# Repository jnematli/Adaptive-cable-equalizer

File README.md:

# GS3440-Adaptive-cable-equalizer
This project was a part of my Hardware Design course at KU Leuven Campus Group T. The PCB was built using Autodesk Eagle.

PCB top side:

PCB bottom side:

50 Ohm transmission line:

75 Ohm transmission line:

Design rules:

•	The outputs should be symmetrical, the transmission lines at the output should be of the same size.

•	Put components closer to the IC to minimize loop area.

•	Put decoupling capacitors for Vcc to reduce noise.

•	Put transistor to the side of the PCB for the possibility to attach a heat sink.

•	Thermal spacing (already mentioned in the DRC).

## License

All design files in this repository are released under the [GNU General Public License version 3 (GPL-3.0)](LICENSE). They can be freely used for personal projects where this device can be of use.

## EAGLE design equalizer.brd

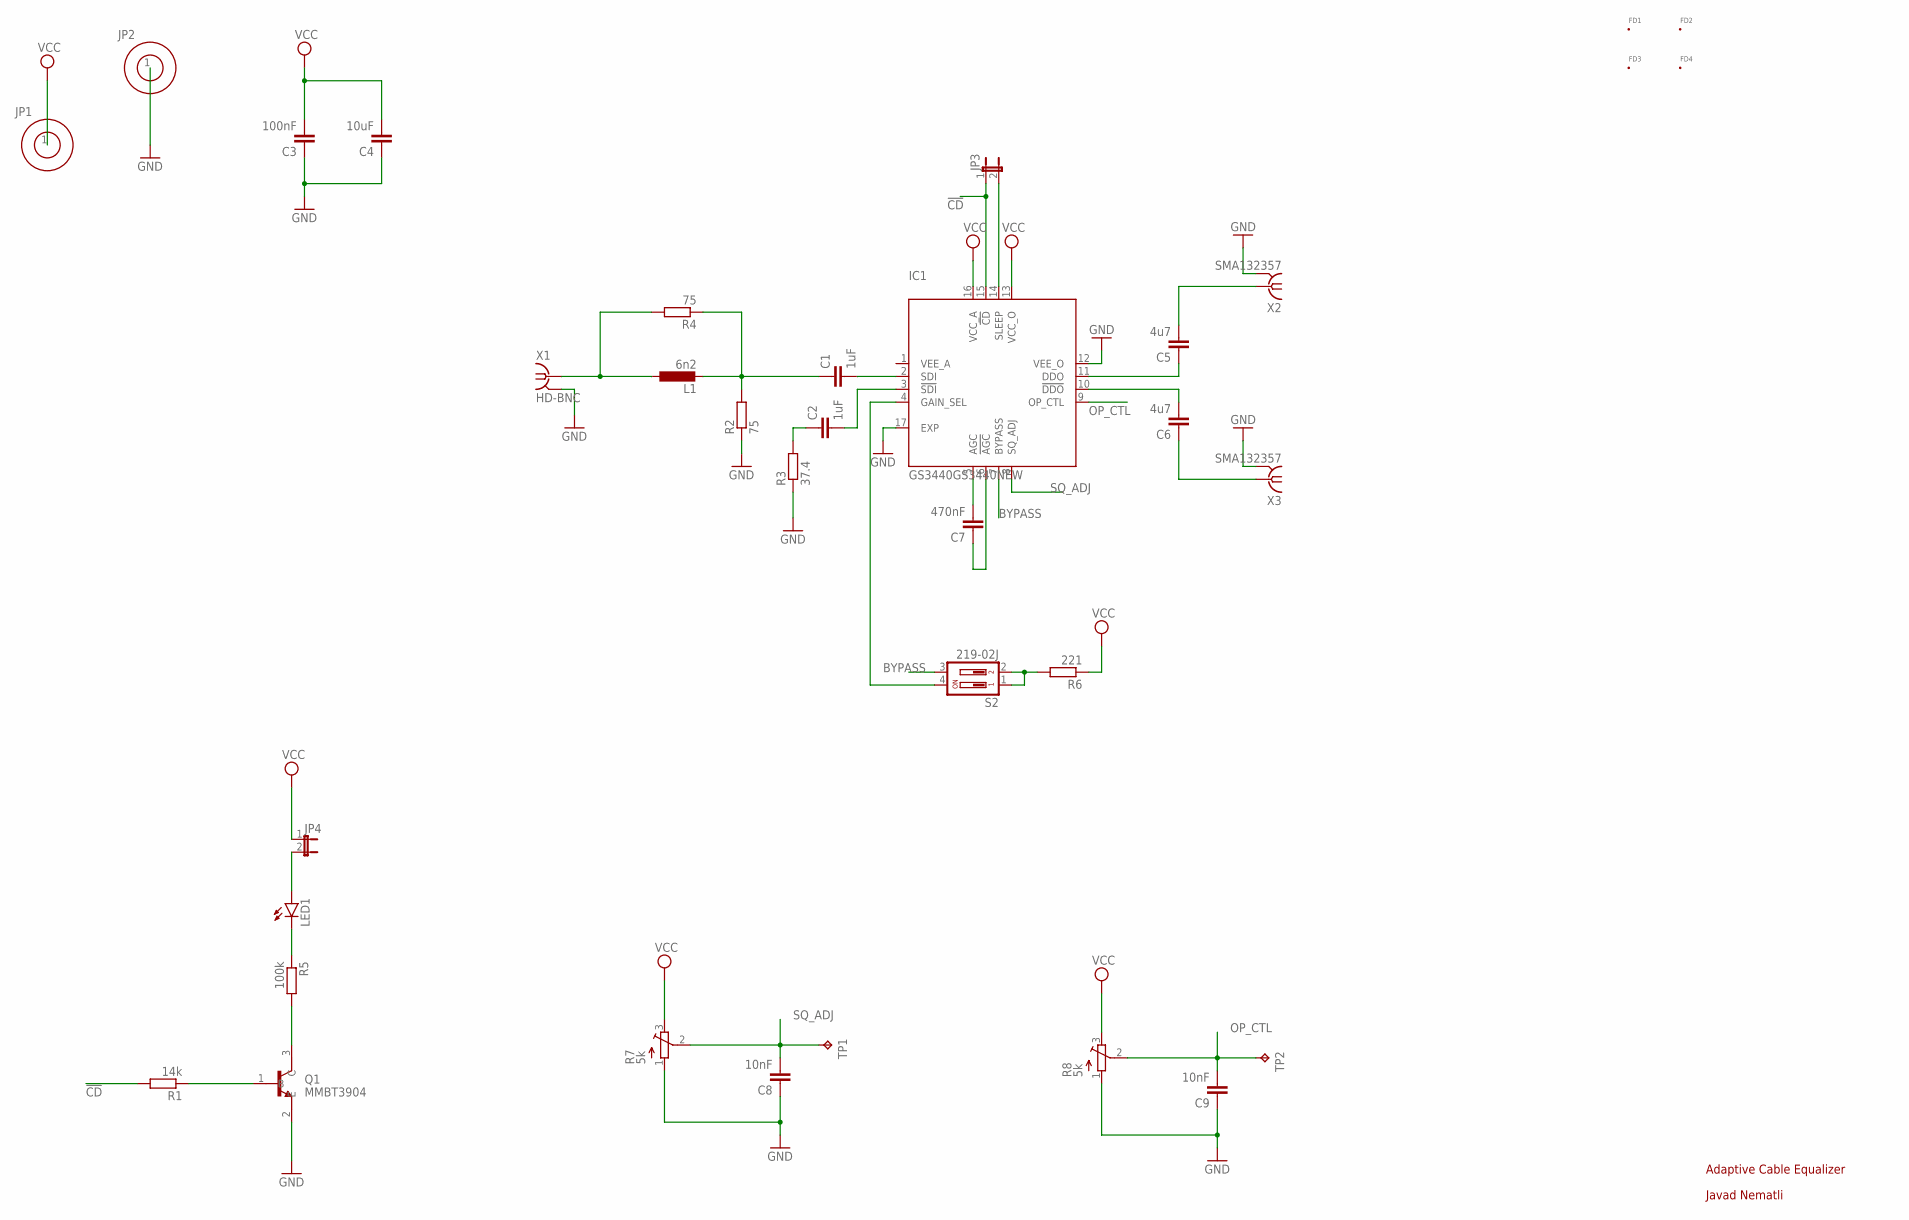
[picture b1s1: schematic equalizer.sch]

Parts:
C1, C2: 1uF; 0402
C3: 100nF; 0402
C4: 10uF; 0402
C5, C6: 4u7; 0402
C7: 470nF; 0402
C8, C9: 10nF; 0402
FD1, FD2, FD3, FD4: FID_20MIL; FID_020
IC1: GS3440GS3440NEW; QFN65P400X400X90-17T260N
JP1, JP2: 4MMSOCKET; 4MM
JP3, JP4: JP1E; JP1
L1: 6n2; 0402
LED1: LEDCHIP-LED0805; CHIP-LED0805
Q1: MMBT3904; SOT95P240X120-3N
R1: 14k; 0402
R2, R4: 75; 0402
R3: 37.4; 0402
R5: 100k; 0402
R6: 221; 0402
R7, R8: 5k; 3223W
S2: 219-02J; CTS-219-02J
TP1, TP2: TPTP06R; TP06R
X1: HD-BNC; 034_1018_12G
X2, X3: SMA132357; SMA

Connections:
!CD: IC1.15 (!CD), JP3.1, R1.2
BYPASS: IC1.7 (BYPASS), S2.3
GND: C3.1, C4.1, C8.1, C9.1, IC1.12 (VEE_O), IC1.17 (EXP), JP2.1, Q1.2 (E), R2.1, R3.1, R7.1 (A), R8.1 (A), X1.G@1 (2), X1.G@2 (2), X1.G@3 (2), X1.G@4 (2), X2.G@1 (2), X2.G@2 (2), X2.G@3 (2), X2.G@4 (2), X3.G@1 (2), X3.G@2 (2), X3.G@3 (2), X3.G@4 (2)
unnamed: C1.2, IC1.2 (SDI)
unnamed: C1.1, L1.2, R2.2, R4.1
unnamed: C2.1, R3.2
unnamed: C2.2, IC1.3 (!SDI)
unnamed: L1.1, R4.2, X1.P$1 (1)
unnamed: C5.1, IC1.11 (DDO)
unnamed: C5.2, X2.1
unnamed: C6.2, IC1.10 (!DDO)
unnamed: C6.1, X3.1
unnamed: C7.2, IC1.5 (AGC)
unnamed: C7.1, IC1.6 (!AGC)
unnamed: Q1.1 (B), R1.1
unnamed: IC1.14 (SLEEP), JP3.2
unnamed: JP4.2, LED1.A
unnamed: LED1.C, R5.1
unnamed: Q1.3 (C), R5.2
unnamed: IC1.4 (GAIN_SEL), S2.4
unnamed: R6.2, S2.1, S2.2
OP_CTL: C9.2, IC1.9 (OP_CTL), R8.2 (S), TP2.TP
SQ_ADJ: C8.2, IC1.8 (SQ_ADJ), R7.2 (S), TP1.TP
VCC: C3.2, C4.2, IC1.13 (VCC_O), IC1.16 (VCC_A), JP1.1, JP4.1, R6.1, R7.3 (E), R8.3 (E)
VEE_A: IC1.1 (VEE_A)

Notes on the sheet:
Adaptive Cable Equalizer
Javad Nematli

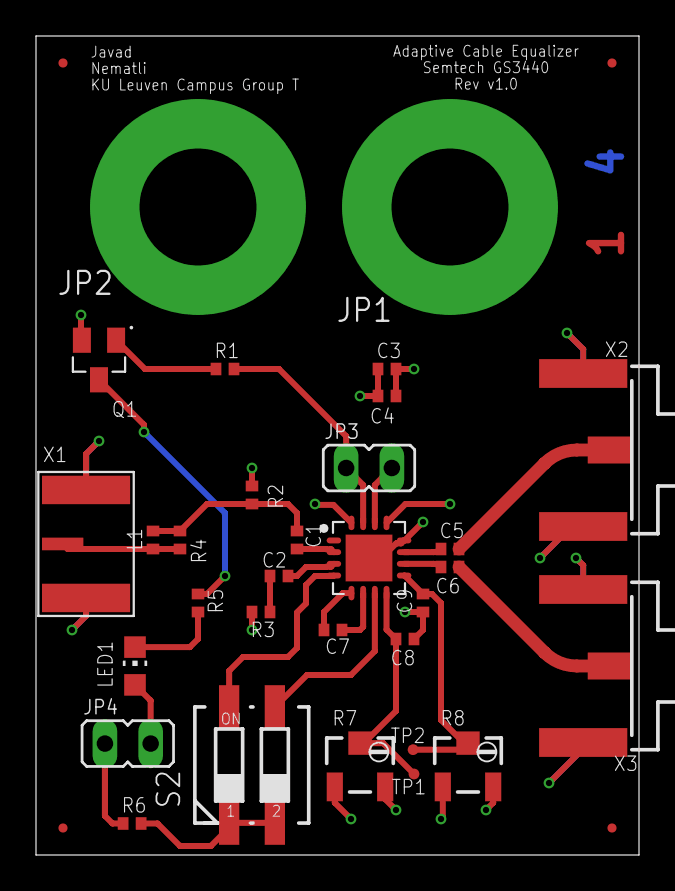
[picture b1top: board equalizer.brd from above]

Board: 4 copper layers, 33.5 x 45.5 mm, 35 parts (0 on the bottom side), 24 nets.

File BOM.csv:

Qty;Value;Device;Package;Parts;Description;AVAILABILITY;BOM;DESCRIPTION;MF;MP;MPN;OC_FARNELL;OC_NEWARK;PACKAGE;POPULARITY;PRICE;TP_SIGNAL_NAME
2;;4MMSOCKET;4MM;JP1, JP2;4MM SOCKET;;;;;;;;;;;;
2;;JP1E;JP1;JP3, JP4;JUMPER;;;;;;;;;;61;;
1;;LEDCHIP-LED0805;CHIP-LED0805;LED1;LED;;;;;;;;;;68;;
1;100k;R0402;402;R5;;;;;;;;;;;;;
1;100nF;C0402;402;C3;;;;;;;;;;;;;
2;10nF;C0402;402;C8, C9;;;;;;;;;;;;;
1;10uF;C0402;402;C4;;;;;;;;;;;;;
1;14k;R0402;402;R1;;;;;;;;;;;;;
2;1uF;C0402;402;C1, C2;;;;;;;;;;;;;
1;219-02J;219-02J;CTS-219-02J;S2;Surface Mount DIP Switch Series 219 SMT;;;;;;;unknown;unknown;;;;
1;221;R0402;402;R6;;;;;;;;;;;;;
1;37.4;R0402;402;R3;;;;;;;;;;;;;
1;470nF;C0402;402;C7;;;;;;;;;;;;;
2;4u7;C0402;402;C5, C6;;;;;;;;;;;;;
2;5k;TRIM_EU-3223W;3223W;R7, R8;POTENTIOMETER;;;;;;;;;;0;;
1;6n2;L0402;402;L1;;;;;;;;;;;;;
2;75;R0402;402;R2, R4;;;;;;;;;;;;;
4;FID_20MIL;FID_20MIL;FID_020;FD1, FD2, FD3, FD4;Fiducial marks. Top and Bottom copper with stop mask;;;;;;;;;;;;
1;GS3440GS3440NEW;GS3440GS3440NEW;QFN65P400X400X90-17T260N;IC1;Adaptive Cable Equalizer;;;;;;;;;;;;
1;HD-BNC;HD-BNC;034_1018_12G;X1;HD BNC 75 Ohm;;;;;;;;;;;;
1;MMBT3904;MMBT3904;SOT95P240X120-3N;Q1;MMBT3904 Series 40 V CE Breakdown 0.2 A NPN General Purpose Amplifier - SOT-23 Check availability;;; Bipolar (BJT) Transistor NPN 40V 200mA 300MHz 300mW Surface Mount SOT-23-3 ;STMicroelectronics;MMBT3904;;;;SOT-23 ON;;None;
2;SMA132357;SMA132357;SMA;X2, X3;SMA 50 Ohm End Launch Jack Receptacle - Round Contact;;;;;;;;;;;;
2;TPTP06R;TPTP06R;TP06R;TP1, TP2;Test pad;;;;;;;;;;1;;
